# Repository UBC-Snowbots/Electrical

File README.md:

# UBC Rover Electrical Subteam Repository

Work is organized year by year (For now?)

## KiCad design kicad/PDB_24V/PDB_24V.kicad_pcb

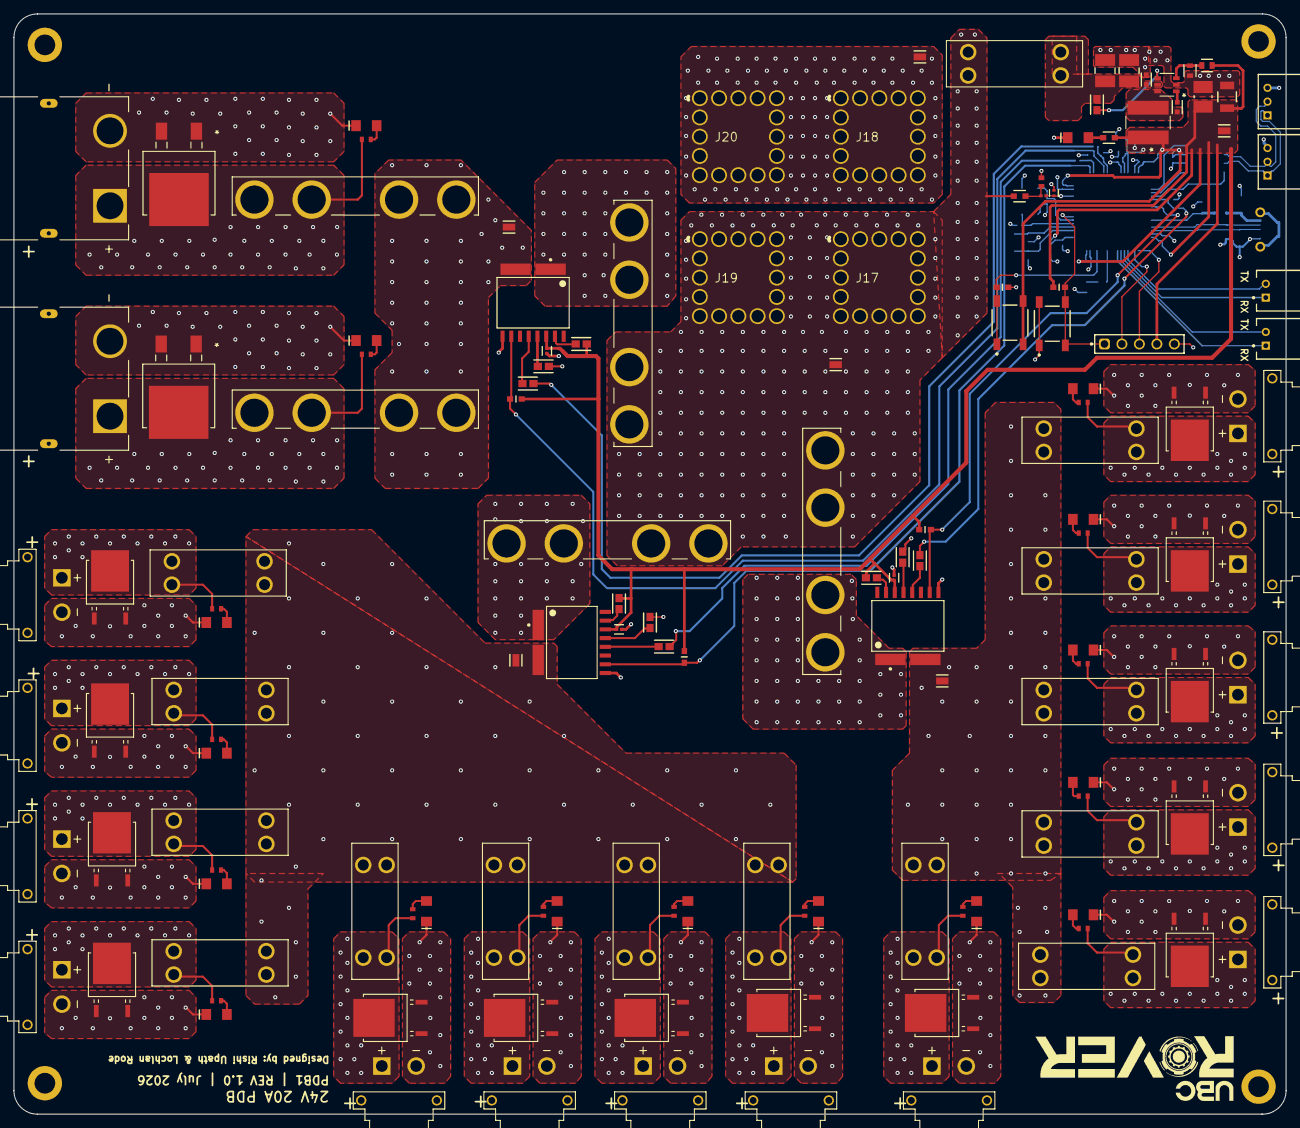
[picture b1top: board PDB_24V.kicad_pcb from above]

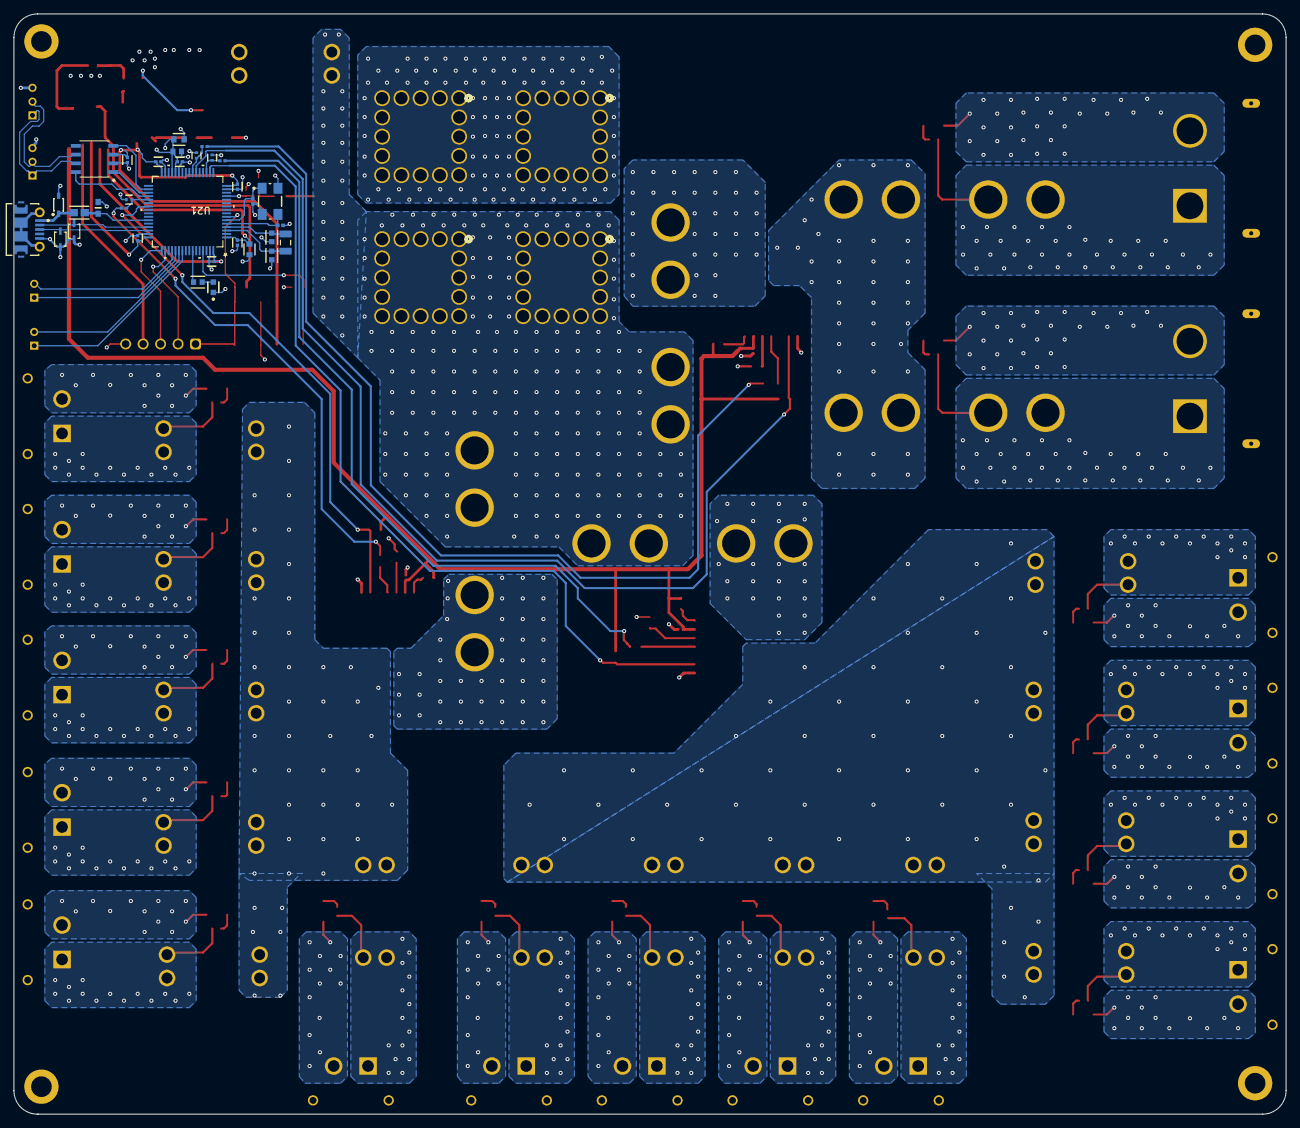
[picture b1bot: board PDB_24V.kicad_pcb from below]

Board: 4 copper layers, 185.0 x 160.0 mm, 170 parts (32 on the bottom side), 90 nets.

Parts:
C1, C4: CGA3E3X8R1H104K080AB; FP-CGA3E-0_3-0_1-MFG
C2, C3: 12105C475KAT2A; FP-1210-L_3_3_0_4-W_2_5_0-IPC_A
C5: UMK325BJ106MM-T; TAYO-C1210-2_M
C6: GRM32ER61E226KE15L; FP-GRM32-MFG
C7, C8, C9, C10, C12, C13, C14, C15, C16, C23: CL05B104KA5NNNC; FP-CL830-IPC_C
C11: GRM188R61E475KE11D; FP-GRM188-0_15-MFG
C17, C18: GRM1555C1H180JA01D; CAPC1005X55X25LL05T10
C19, C20: CL10C060DB8NNNC; FP-CL10-IPC_C
C21: CC0603KRX7R7BB105; FP-CC0603-DA-MFG
C22: GCM188R71H103KA37D; CAPC1608X90X35LL10T15
C24, C25, C26, C27: GRM1555C1H102JA01D; FP-GRM155-0_05-MFG
D1, D2, D3, D4, D5, D6, D7, D8, D9, D10, D11, D12, D13, D14, D15, D16, D17: 150120VS75000; WL-SMCW_1206_150120xx75000
D18: LTST-C191KGKT; FP-LTST-C191KGKT-MFG
D19: TSD05DYFR; FP-DYF0002A-MFG
F1, F5, F6, F7, F10, F11, F12, F13, F14, F15, F16, F17, F18, F19, F20: 3557-2; FUSE_3557-2
F2, F3, F4, F8, F9: 3555-2; FUSE_3555-2
J1, J2, J3, J6, J7, J8, J9, J10, J11, J12, J13, J14, J15, J16: XT30PW-F; AMASS_XT30PW-F
J4, J5: XT90PW-F; AMASS_XT90PW-F
J17, J18, J19, J20: S93515; CONN16_S93515_WRE
J21, J22: S3B-PH-K-S(LF)(SN); FP-S3B-PH-K-S_LF_SN-MFG
J23: 1050170001; USB-MICRO-B_V
J24, J25, J26, J27, J28, J29: S2761-46R; FP-S2761-46R-MFG
L1: SRN6045-8R2Y; IND_BOURNS_SRN6045
P1, P2: S2B-PH-K-S(LF)(SN); JST-S2B-PH-K-S_V
P3: 61300511121
R1, R7, R8, R10, R30, R38, R39, R40, R41, R42, R43: RMCF0603ZT0R00; FP-RMCF0603-IPC_A
R2: AC0603FR-07130RL; FP-AC0603-MFG
R3: CRCW060369K8FKEB; FP-CRCW0603-e3-MFG
R4: RMCF0603FT22K1; FP-RMCF0603-MFG
R5, R6, R9, R28, R29, R31: RC0603FR-0710KL; FP-RC0603-0_55-MFG
R11, R12, R13, R14, R15, R16, R17, R18, R19, R20, R21, R22, R23, R24, R25, R26: RC0603FR-072K2L; RESC1608X55X25LL10T15
R27: CRGCQ0603J220R; FP-CRGCQ0603-IPC_C
R32, R33, R34, R36: RC0402FR-07150RL; RESC1005X40X25LL05T10
R35: AC0603FR-0718KL; FP-AC0603-MFG
R37: ERJ-3EKF2001V; RESC1608X55X30LL15T15
SW1, SW2: 8-1437565-1; FP-8-1437565-1-MFG
U1: LMR54410DBVR; SOT-23-6-DBV_TEX
U2, U3, U4: TMCS1123B1AQDVGR; DVG0010A-MFG
U5, U6, U7, U10, U11, U12, U13, U14, U15, U16, U17, U18, U19, U20: SDT30B100D1-13; TO252_DIO
U8, U9: V40DL45-M3I; SOT_45-M3I_VIS
U21: STM32G491RET6; LQFP64_10X10_STM
U22: TCAN3404DRQ1; SOIC8_D_TEX
U23, U24: D5V0L1B2WS-7; SOD323_DIO
Y1: ABM3C-16.000MHZ-D4Y-T; FP-ABM3C-MFG
Y2: ABS07-166-32.768KHZ-T; EPSON-FC-135_V

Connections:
3.3V: C5.2, C6.2, C7.2, C8.2, C9.2, C10.2, C11.2, C12.2, C13.2, C14.2, C15.2, C16.2, C21.2, C22.2, C23.2, J26.1, L1.1, P3.4, R2.1, R3.2, R5.2, R6.2, R9.2, R28.2, R40.1, R41.1, R43.1, SW1.3, SW1.4, U2.8, U3.8, U4.8, U21.1, U21.16, U21.28, U21.29, U21.32, U21.48, U21.64, U22.3
3V3_CB: C1.1, U1.1
3V3_EN: R1.2, U1.4
3V3_FB: R3.1, R4.1, U1.3
3V3_SW: C1.2, L1.2, U1.6
5V_UART_RX: P2.1, U21.55
5V_UART_TX: P2.2, U21.54
18V_12V_UART_RX: P1.1, U21.53
18V_12V_UART_TX: P1.2, U21.52
24V: F1.1_1, F1.1_2, F2.1_1, F2.1_2, F3.1_1, F3.1_2, F4.1_1, F4.1_2, J17.1, J17.2, J17.3, J17.4, J17.5, J17.6, J17.7, J17.8, J17.9, J17.10, J17.11, J17.12, J17.13, J17.14, J17.15, J17.16, J19.1, J19.2, J19.3, J19.4, J19.5, J19.6, J19.7, J19.8, J19.9, J19.10, J19.11, J19.12, J19.13, J19.14, J19.15, J19.16, J24.1, R35.2
24V_ARM1: F8.2_1, F8.2_2, J4.P, R14.2, U8.3
24V_ARM2: F9.2_1, F9.2_2, J5.P, R15.2, U9.3
24V_ARM_F: F2.2_1, F2.2_2, U2.1
24V_ARM_S: F8.1_1, F8.1_2, F9.1_1, F9.1_2, J28.1, U2.2
24V_BUCK: C2.1, C3.1, C4.2, F1.2_1, F1.2_2, R1.1, U1.5
24V_CHASSIS_F: F3.2_1, F3.2_2, U3.1
24V_CHASSIS_S: F5.1_1, F5.1_2, F6.1_1, F6.1_2, F7.1_1, F7.1_2, F10.1_1, F10.1_2, F11.1_1, F11.1_2, F12.1_1, F12.1_2, J27.1, U3.2
24V_LIGTHING: F14.2_1, F14.2_2, J10.P, R20.2, U14.3
24V_M0: F5.2_1, F5.2_2, J1.P, R11.2, U5.3
24V_M1: F6.2_1, F6.2_2, J2.P, R12.2, U6.3
24V_M2: F7.2_1, F7.2_2, J3.P, R13.2, U7.3
24V_M3: F10.2_1, F10.2_2, J6.P, R16.2, U10.3
24V_M4: F11.2_1, F11.2_2, J7.P, R17.2, U11.3
24V_M5: F12.2_1, F12.2_2, J8.P, R18.2, U12.3
24V_MISC_F: F4.2_1, F4.2_2, U4.1
24V_MISC_S: F13.1_1, F13.1_2, F14.1_1, F14.1_2, F15.1_1, F15.1_2, F16.1_1, F16.1_2, F17.1_1, F17.1_2, F18.1_1, F18.1_2, F19.1_1, F19.1_2, F20.1_1, F20.1_2, J29.1, U4.2
24V_PoE: F18.2_1, F18.2_2, J14.P, R24.2, U18.3
24V_SCIENCE: F13.2_1, F13.2_2, J9.P, R19.2, U13.3
24V_SPARE_1: F15.2_1, F15.2_2, J11.P, R21.2, U15.3
24V_SPARE_2: F16.2_1, F16.2_2, J12.P, R22.2, U16.3
24V_SPARE_3: F17.2_1, F17.2_2, J13.P, R23.2, U17.3
24V_SPARE_4: F19.2_1, F19.2_2, J15.P, R25.2, U19.3
24V_SPARE_5: F20.2_1, F20.2_2, J16.P, R26.2, U20.3
ARM_ALERT: R5.1, U2.4, U21.22
ARM_SENSE: R7.2, R34.1
ARM_SENSE_IN: C26.2, R34.2, U21.23
B3.3V_LED: D1.2, R2.2
B24_Voltage: C27.2, R36.2, U21.13
B24_Voltage_In: R35.1, R36.1, R37.2
CAN_N: J21.2, J22.2, U22.6
CAN_P: J21.1, J22.1, U22.7
CAN_RX: U21.34, U22.4
CAN_STB: U21.36, U22.8
CAN_TX: U21.35, U22.1
CHASSIS_ALERT: R6.1, U3.4, U21.39
CHASSIS_SENSE: R8.2, R33.1
CHASSIS_SENSE_IN: C25.2, R33.2, U21.37
GND: C2.2, C3.2, C4.1, C5.1, C6.1, C7.1, C8.1, C9.1, C10.1, C11.1, C12.1, C13.1, C14.1, C15.1, C16.1, C17.1, C18.1, C19.1, C20.1, C21.1, C22.1, C23.1, C24.1, C25.1, C26.1, C27.1, D1.1, D2.1, D3.1, D4.1, D5.1, D6.1, D7.1, D8.1, D9.1, D10.1, D11.1, D12.1, D13.1, D14.1, D15.1, D16.1, D17.1, D18.1, D19.2, J1.N, J2.N, J3.N, J4.N, J5.N, J6.N, J7.N, J8.N, J9.N, J10.N, J11.N, J12.N, J13.N, J14.N, J15.N, J16.N, J18.1, J18.2, J18.3, J18.4, J18.5, J18.6, J18.7, J18.8, J18.9, J18.10, J18.11, J18.12, J18.13, J18.14, J18.15, J18.16, J20.1, J20.2, J20.3, J20.4, J20.5, J20.6, J20.7, J20.8, J20.9, J20.10, J20.11, J20.12, J20.13, J20.14, J20.15, J20.16, J21.3, J22.3, J23.5, J23.6, J23.7, J23.8, J23.9, J23.10, J23.11, J25.1, P3.5, R4.2, R29.1, R31.1, R37.1, R38.2, R39.2, R42.2, SW2.1, SW2.2, U1.2, U2.3, U3.3, U4.3, U5.1, U5.2, U6.1, U6.2, U7.1, U7.2, U8.1, U8.2, U9.1, U9.2, U10.1, U10.2, U11.1, U11.2, U12.1, U12.2, U13.1, U13.2, U14.1, U14.2, U15.1, U15.2, U16.1, U16.2, U17.1, U17.2, U18.1, U18.2, U19.1, U19.2, U20.1, U20.2, U21.15, U21.27, U21.31, U21.47, U21.63, U22.2, U23.2, U24.2, Y1.2, Y1.4
HSE_OSC_IN: C18.2, U21.5, Y1.3
HSE_OSC_OUT: C17.2, U21.6, Y1.1
LED_DEBUG_1: D18.2, R27.1
LED_DEBUG_2: R27.2, U21.58
LSE_OSC_IN: C20.2, U21.3, Y2.2
LSE_OSC_OUT: C19.2, U21.4, Y2.1
MCU_BOOT0: R29.2, SW1.1, SW1.2, U21.61
MCU_NRST: P3.1, R28.1, SW2.3, SW2.4, U21.7
MISC_ALERT: R9.1, U4.4, U21.18
MISC_SENSE: R10.2, R32.1
MISC_SENSE_IN: C24.2, R32.2, U21.19
NetD2_2: D2.2, R11.1
NetD3_2: D3.2, R12.1
NetD4_2: D4.2, R13.1
NetD5_2: D5.2, R14.1
NetD6_2: D6.2, R15.1
NetD7_2: D7.2, R16.1
NetD8_2: D8.2, R17.1
NetD9_2: D9.2, R18.1
NetD10_2: D10.2, R19.1
NetD11_2: D11.2, R20.1
NetD12_2: D12.2, R21.1
NetD13_2: D13.2, R22.1
NetD14_2: D14.2, R23.1
NetD15_2: D15.2, R24.1
NetD16_2: D16.2, R25.1
NetD17_2: D17.2, R26.1
NetR7_1: R7.1, U2.6
NetR8_1: R8.1, U3.6
NetR10_1: R10.1, U4.6
NetR38_1: R38.1, U2.7
NetR39_1: R39.1, U3.7
NetR40_2: R40.2, U2.9
NetR41_2: R41.2, U3.9
NetR42_1: R42.1, U4.7
NetR43_2: R43.2, U4.9
SWD_SWCLK: P3.2, U21.50
SWD_SWDIO: P3.3, U21.49
USB_D_N: J23.2, U21.45, U23.1
USB_D_P: J23.3, U21.46, U24.1
VBUS: D19.1, J23.1, R30.2
VBUS_SENSE: R30.1, R31.2, U21.43

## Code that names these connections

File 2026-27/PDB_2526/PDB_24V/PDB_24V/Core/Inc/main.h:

/* USER CODE BEGIN Header */
/**
  ******************************************************************************
  * @file           : main.h
  * @brief          : Header for main.c file.
  *                   This file contains the common defines of the application.
  ******************************************************************************
  * @attention
  *
  * Copyright (c) 2026 STMicroelectronics.
  * All rights reserved.
  *
  * This software is licensed under terms that can be found in the LICENSE file
  * in the root directory of this software component.
  * If no LICENSE file comes with this software, it is provided AS-IS.
  *
  ******************************************************************************
  */
/* USER CODE END Header */

/* Define to prevent recursive inclusion -------------------------------------*/
#ifndef __MAIN_H
#define __MAIN_H

#ifdef __cplusplus
extern "C" {
#endif

/* Includes ------------------------------------------------------------------*/
#include "stm32g4xx_hal.h"

/* Private includes ----------------------------------------------------------*/
/* USER CODE BEGIN Includes */

/* USER CODE END Includes */

/* Exported types ------------------------------------------------------------*/
/* USER CODE BEGIN ET */

/* USER CODE END ET */

/* Exported constants --------------------------------------------------------*/
/* USER CODE BEGIN EC */

/* USER CODE END EC */

/* Exported macro ------------------------------------------------------------*/
/* USER CODE BEGIN EM */

/* USER CODE END EM */

/* Exported functions prototypes ---------------------------------------------*/
void Error_Handler(void);

/* USER CODE BEGIN EFP */

/* USER CODE END EFP */

/* Private defines -----------------------------------------------------------*/
#define SENSE_24V_Pin GPIO_PIN_1
#define SENSE_24V_GPIO_Port GPIOA
#define MISC_ALERT_Pin GPIO_PIN_4
#define MISC_ALERT_GPIO_Port GPIOA
#define MISC_SENSE_Pin GPIO_PIN_5
#define MISC_SENSE_GPIO_Port GPIOA
#define ARM_ALERT_Pin GPIO_PIN_4
#define ARM_ALERT_GPIO_Port GPIOC
#define ARM_SENSE_Pin GPIO_PIN_5
#define ARM_SENSE_GPIO_Port GPIOC
#define CAN_STB_Pin GPIO_PIN_14
#define CAN_STB_GPIO_Port GPIOB
#define CHASSIS_SENSE_Pin GPIO_PIN_15
#define CHASSIS_SENSE_GPIO_Port GPIOB
#define CHASSIS_ALERT_Pin GPIO_PIN_7
#define CHASSIS_ALERT_GPIO_Port GPIOC
#define VBUS_SENSE_Pin GPIO_PIN_9
#define VBUS_SENSE_GPIO_Port GPIOA
#define DEBUG_LED_Pin GPIO_PIN_5
#define DEBUG_LED_GPIO_Port GPIOB

/* USER CODE BEGIN Private defines */

/* USER CODE END Private defines */

#ifdef __cplusplus
}
#endif

#endif /* __MAIN_H */

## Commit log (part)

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2026-01-31 Initial C firmware for motor control using Nucleo.
2026-02-01 Added breaks and commands for L and R side control
2026-02-02 Added protections for invalid commands
2026-02-20 Added ctype.h for character validation
2026-02-21 Improved readability. Fixed critical logic errors.
2026-03-08 Improved readability
2026-03-15 Implemented debugging tests
2026-03-29 Added get_speed command in RPM
2026-03-29 Contains IOC and other setup files
2026-03-29 Removed code reduncancy. Updated README
